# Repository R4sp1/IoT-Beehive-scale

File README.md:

# IoT Beehive scale :honeybee:

### What is it?

  The aim of this graduation work is to manufacture bee hive weight measuring equipment with
  information transfer via Internet of Things network Sigfox. It deals with Internet of Things
  technology, weight sensors, energy saving in battery powered devices, PCB designing in the
  EAGLE program and the production of device to monitor the current weight, temperature and
  humidity inside and around the bee hive. Information processing is provided by
  microcontroller ATmega 328U placed on the Arduino pro mini and programmed in Wiring
  language in Arduino IDE.

### Why is it?

  The repository contains code for my high school graduation project and the SOČ competition (High school project competition).

### Co je to?

  Cílem této maturitní práce je výroba zařízení pro měření hmotnosti včelího úlu s přenosem
  informací pomocí sítě internetu věcí Sigfox. Zabývá se technologií internetu věcí, váhových
  senzorů, úsporou energie v rámci napájení na baterii, návrhem plošného spoje v programu
  EAGLE a výrobou funkčního zařízení pro sledování aktuální váhy, teploty a vlhkosti uvnitř
  a v okolí včelího úlu. Zpracování informací je zajištěno mikrokontrolerem ATmega 328U
  umístěném na Arduinu pro mini a naprogramovaném v jazyce Wiring v programu Arduino
  IDE.

### Proč je to?

  Repozitář obsahuje kód k maturitnímu projektu a k soutěži SOČ.

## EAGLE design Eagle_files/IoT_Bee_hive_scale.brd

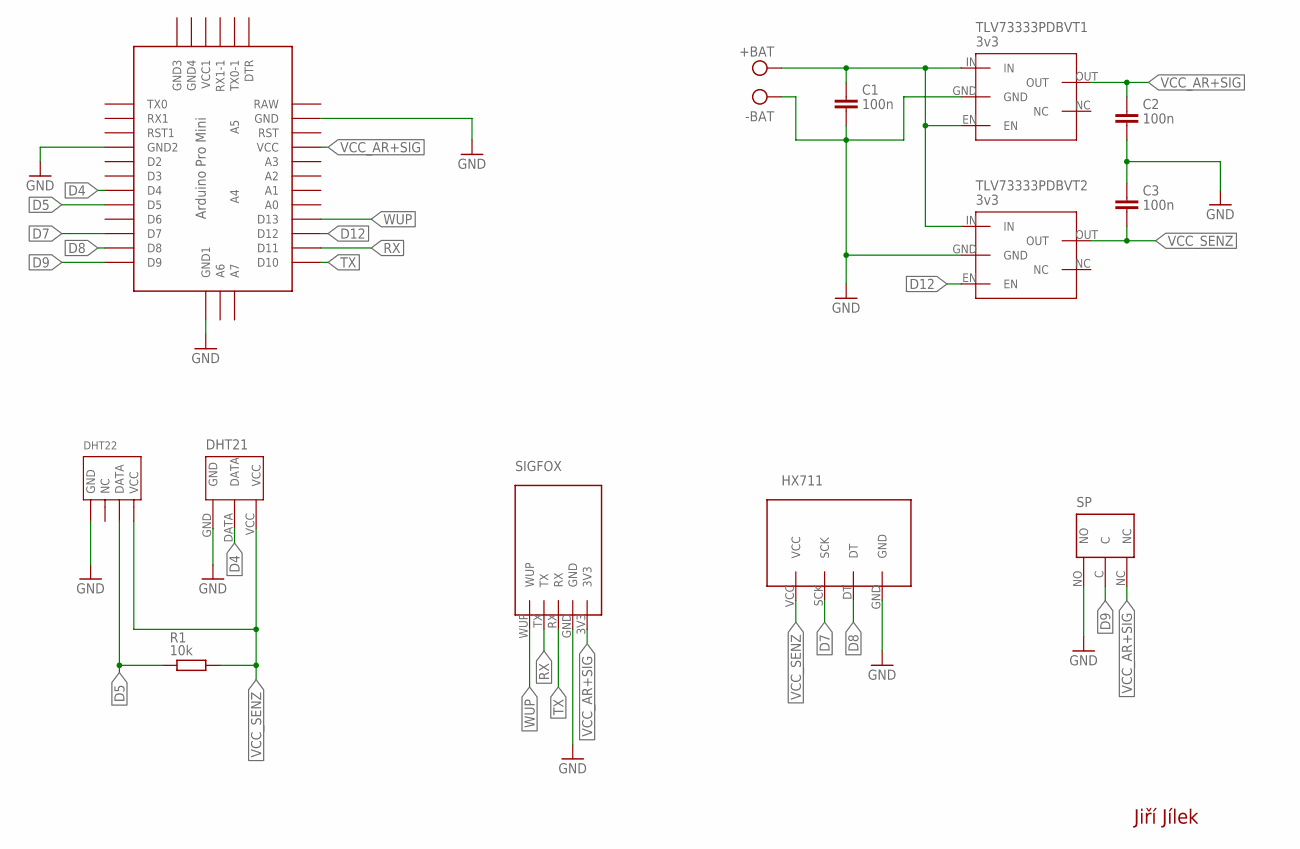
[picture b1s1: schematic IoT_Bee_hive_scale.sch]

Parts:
+BAT: 3.7V; AK300/2
C1, C2, C3: 100n; C1206
DHT21: 0; DHT21
DHT22: DHT22
HX711: 0; HX711
R1: 10k; R0805
SIGFOX: 0; SIGFOX_NODE
SP: 0; MIKROSP
TLV73333PDBVT1, TLV73333PDBVT2: 3v3; SOT95P280X145-5N
U$1: ABK-PRO-MINI

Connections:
D4: DHT21.DATA, U$1.D4
D5: DHT22.DATA, R1.1, U$1.D5
D7: HX711.SCK, U$1.D7
D8: HX711.DT, U$1.D8
D9: SP.C, U$1.D9
D12: TLV73333PDBVT2.EN, U$1.D12
GND: +BAT.2, C1.2, C2.2, C3.1, DHT21.GND, DHT22.GND, HX711.GND, SIGFOX.GND, SP.NO, TLV73333PDBVT1.GND, TLV73333PDBVT2.GND, U$1.GND, U$1.GND1 (GND2), U$1.GND4 (GND1)
RX: SIGFOX.TX, U$1.D11
TX: SIGFOX.RX, U$1.D10
VCC: +BAT.1, C1.1, TLV73333PDBVT1.EN, TLV73333PDBVT1.IN, TLV73333PDBVT2.IN
VCC_AR+SIG: C2.1, SIGFOX.3V3, SP.NC, TLV73333PDBVT1.OUT, U$1.VCC
VCC_SENZ: C3.2, DHT21.VCC, DHT22.VCC, HX711.VCC, R1.2, TLV73333PDBVT2.OUT
WUP: SIGFOX.WUP, U$1.D13

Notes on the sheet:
+BAT
-BAT
Jiří Jílek

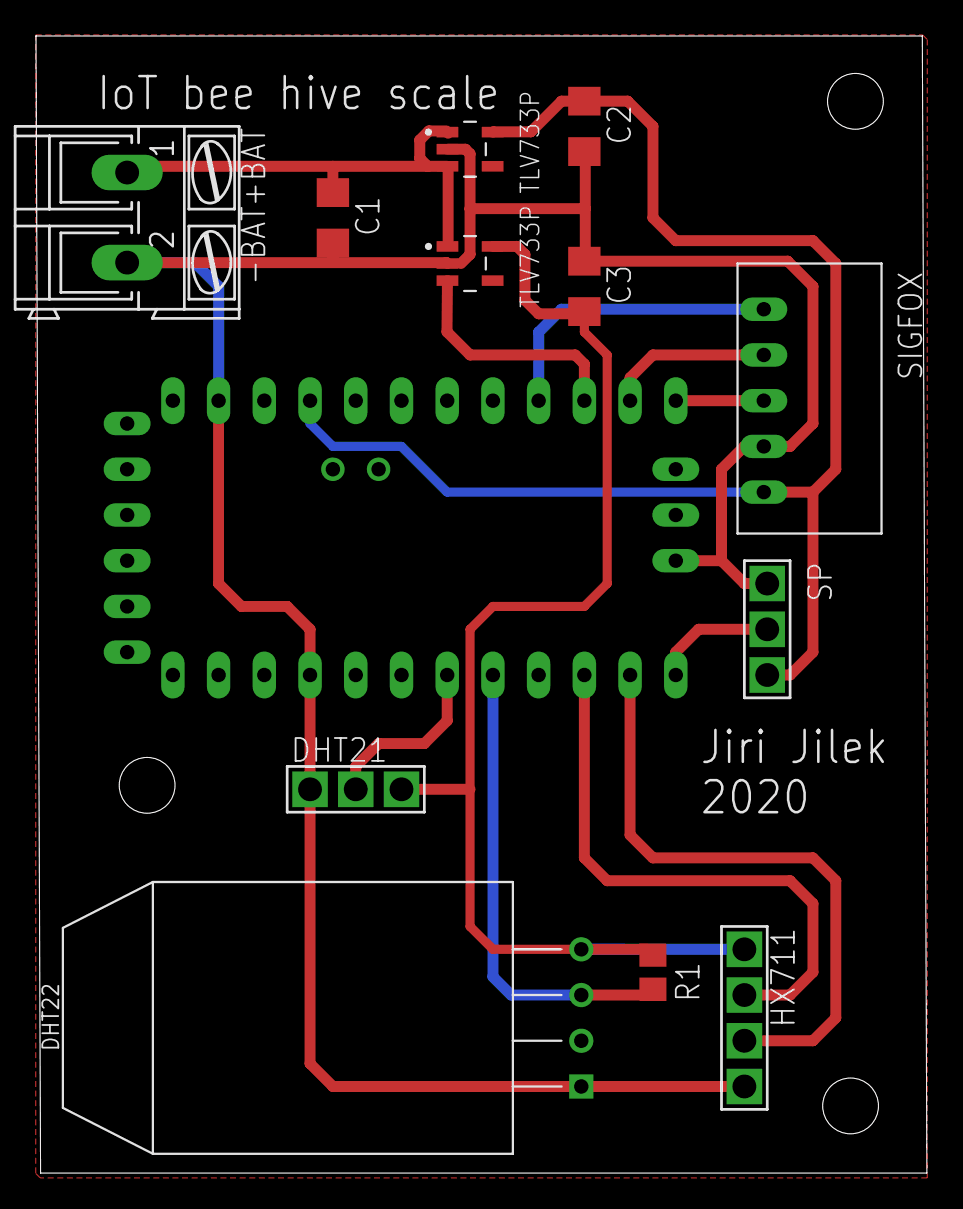
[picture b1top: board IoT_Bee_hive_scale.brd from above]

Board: 2 copper layers, 49.5 x 63.2 mm, 13 parts (0 on the bottom side), 13 nets.
